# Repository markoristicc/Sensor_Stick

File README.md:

# Project Dragonfly Documentation

## Overview 

Project Dragonfly serves as a way to consolidate several low-profile sensors into a single, peripheral device, which attaches via USB to an drone in order to provide an estimation of state while keeping the device as small as possible. In doing so, we hope to create a modular, more cost effective way of providing state estimation, reducing the individual sensor configuration workload for drone manufacturers and hobbyists

The files containing the dragonfly PCB schematic and layout can be found in [PCB](https://github.com/markoristicc/Sensor_Stick/tree/prod/PCB), and the driver code can be found in the [SensorStick_integrated](https://github.com/markoristicc/Sensor_Stick/tree/prod/SensorStick_integrated) folder. This code was developed using the STM32CubeIDE, so that may be most convenient for you, however any embedded C development environment should suffice for flashing the code onto the PCB.  

## Getting Data off the Dragonfly for your own use

If you want to use the Dragonfly simply to collect data, we have provided code to do so, located in [UAVFirmware](https://github.com/markoristicc/Sensor_Stick/tree/prod/UAVFirmware) . If you are not already familiar with ROS, visiting [this](https://docs.ros.org/en/humble/Tutorials.html) documentation may be helpful, specifically the tutorials on creating a workspace, creating a package, writing a simply publisher & subscriber (python), and creating custom msg files. The code we are using assumes that you are running using ROS Humble on Ubuntu 22.02 and are using Python > 3 . 

In essence, this data parses the packet sent by the dragonfly and composes a custom message composed of the following message types: sensor_msgs/Imu, sensor_msgs/MagneticField, sensor_msgs/NavSatTransform, rosflight_msgs/Barometer, and rosflight_msgs/Airspeed. This message is published to the topic 'topic' (which can be changed in UAVFirmware/src/talker_listener/talker_listener/talker.py). To run the publisher enter the following commands into your terminal:

```
source /opt/ros/humble/setup.bash
colcon build --packages-select talker_listener 
```
On a separate terminal run
```
source install/setup.bash
ros2 run talker_listener talkerNode
```

And from there your ROS pubisher will be publishing data from the dragonfly to 'topic' at a rate of 100Hz!

## Performing Visualizations

If you want to perform visualizations using a state estimation computed from the measurements on the board, simply run the code located in [estimationVisualization](https://github.com/markoristicc/Sensor_Stick/tree/prod/estimationVisualization). This code assumes you are running ROS Melodic on Ubuntu 18.02, with Python 2.7 >. The library we use to perform estimation is [robot_localization](http://docs.ros.org/en/noetic/api/robot_localization/html/index.html) and the library for visualization is [RViz](http://wiki.ros.org/rviz). Although you should not need to read through the documentation to perform the visualizations, if you wish to modify any of the code for your own use reading them is **important**.

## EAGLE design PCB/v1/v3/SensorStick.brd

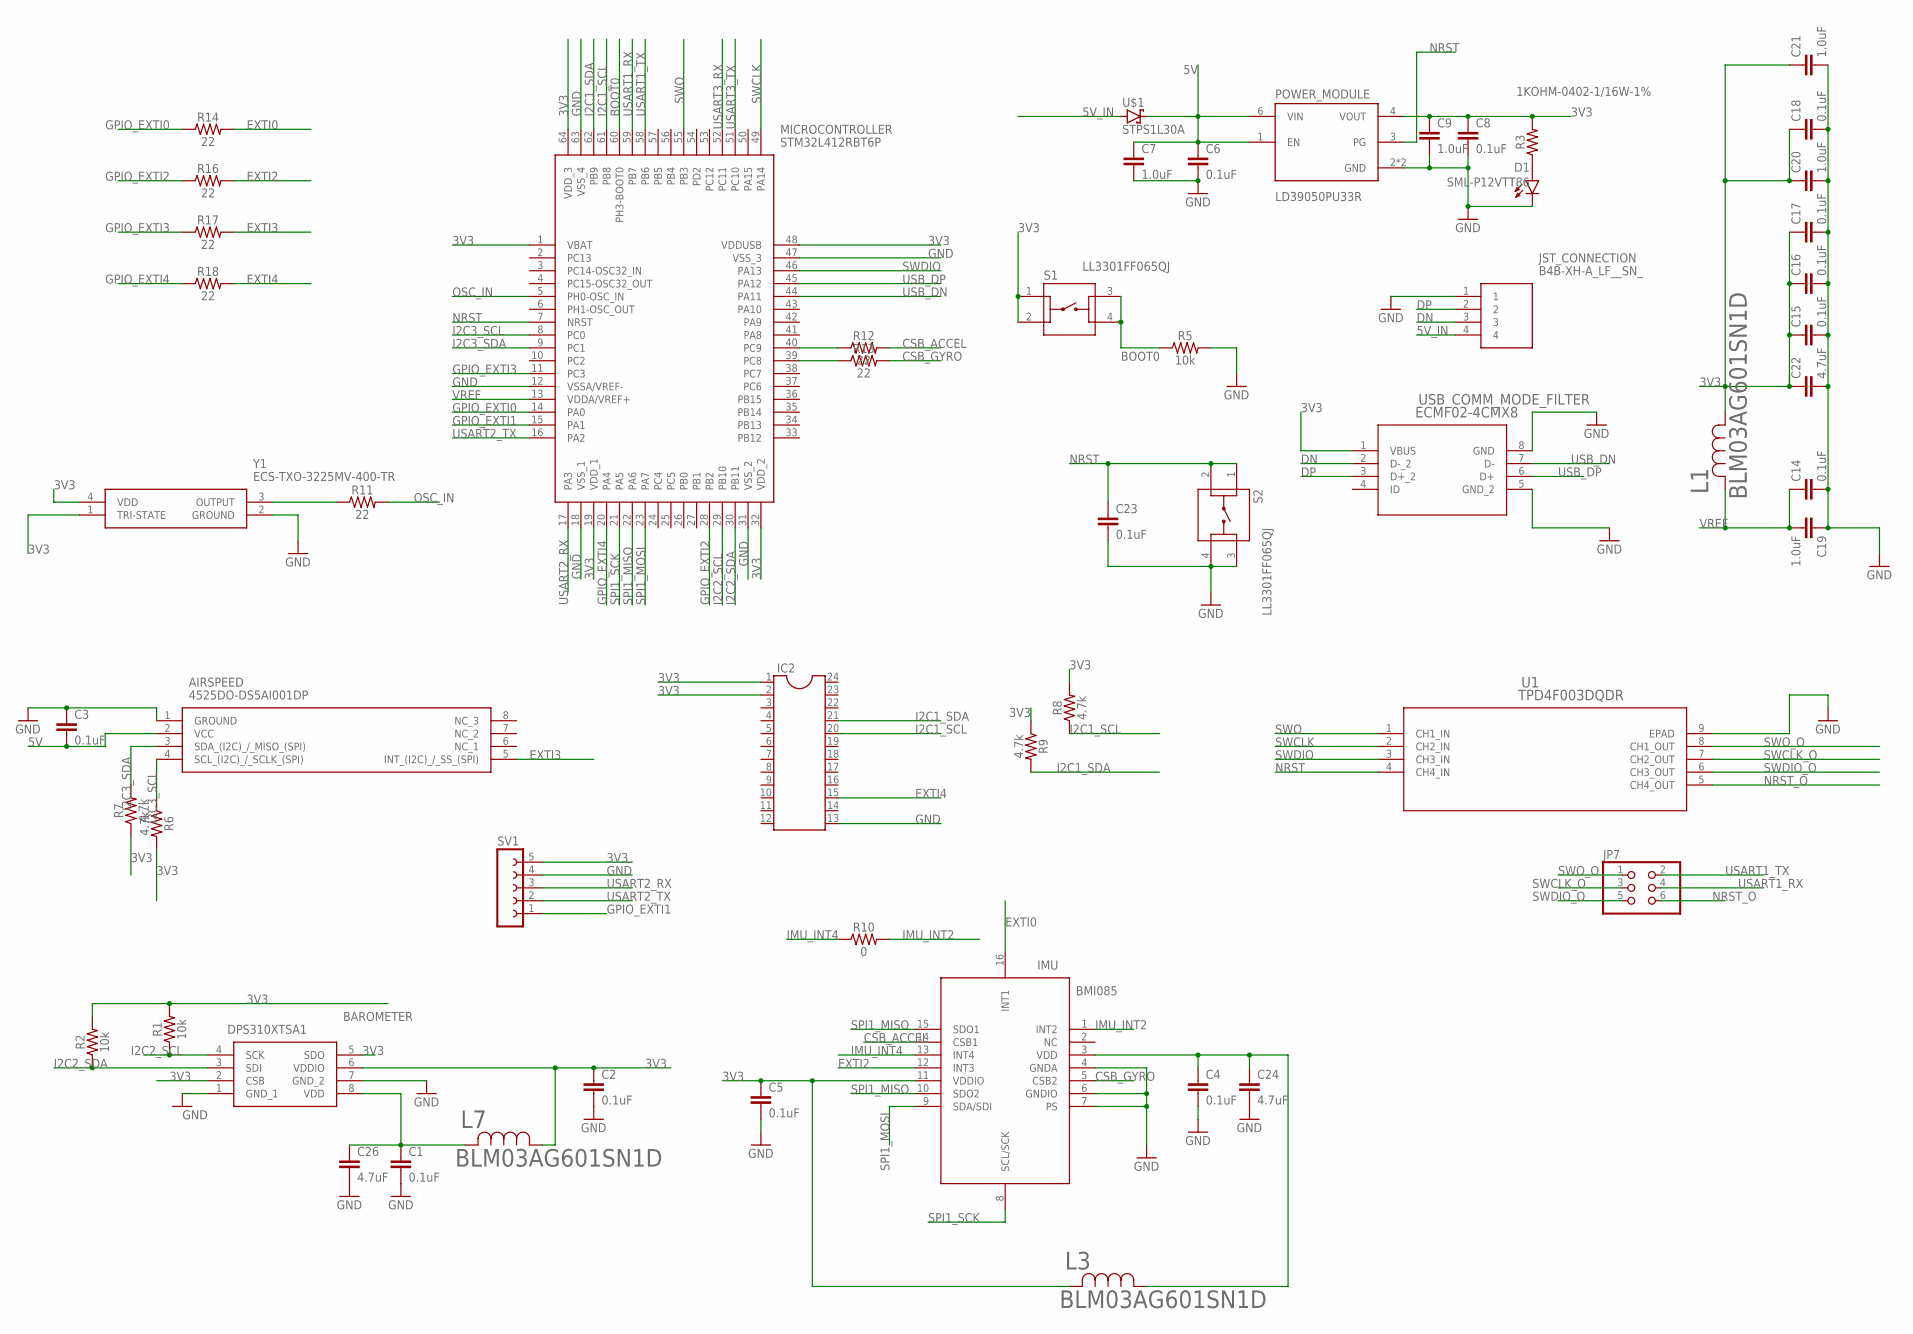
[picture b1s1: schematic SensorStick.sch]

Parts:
AIRSPEED: 4525DO-DS5AI001DP; 4525DO-DS...P
BAROMETER: DPS310XTSA1
C1, C2, C3, C4, C5, C6, C8: 0.1uF; 0402
C7, C9: 1.0uF; 0402
C14, C15, C16, C17, C18, C23: 0.1uF; 0603
C19, C20, C21: 1.0uF; 0805
C22, C24, C26: 4.7uF; 0603
D1: SML-P12VTT86; LED_SML-P11UTT86R
IC2: DIL24-6
IMU: BMI085
JP7: PINHD-2X3; 2X03
JST_CONNECTION: B4B-XH-A_LF__SN_; B4BXHALFSN
L1, L3, L7: BLM03AG601SN1D; IND_BLM03_0201_MUR
MICROCONTROLLER: STM32L412RBT6P; QFP50P1200X1200X160-64N
POWER_MODULE: LD39050PU33R; SON95P300X300X100-7N
R1, R2: 10k; 0402
R3: 1KOHM-0402-1/16W-1%; 0402
R5: 10k; 0603
R6, R7, R8, R9: 4.7k; 0603
R10: 0; 0603
R11, R12, R13, R14, R16, R17, R18: 22; 0402
S1, S2: LL3301FF065QJ
SV1: FE05-1
U1: TPD4F003DQDR; DQD8_1P2X0P4
U$1: STPS1L30A; DIOM5226X223N
USB_COMM_MODE_FILTER: ECMF02-4CMX8; MICRO_QFN-8L_STM
Y1: ECS-TXO-3225MV-400-TR; ECSTXO3225MV400TR

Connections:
3V3: BAROMETER.2 (CSB), BAROMETER.5 (SDO), BAROMETER.6 (VDDIO), C2.1, C5.1, C8.1, C9.1, C15.1, C16.1, C17.1, C18.1, C20.1, C21.1, C22.1, IC2.1, IC2.2, IMU.11 (VDDIO), L1.1, L3.2, L7.1, MICROCONTROLLER.1 (VBAT), MICROCONTROLLER.19 (VDD_1), MICROCONTROLLER.32 (VDD_2), MICROCONTROLLER.48 (VDDUSB), MICROCONTROLLER.64 (VDD_3), POWER_MODULE.4 (VOUT), R1.2, R2.2, R3.2, R6.2, R7.1, R8.2, R9.1, S1.1, S1.2, SV1.5, USB_COMM_MODE_FILTER.1 (VBUS), Y1.1 (TRI-STATE), Y1.4 (VDD)
5V: AIRSPEED.2 (VCC), C3.2, C6.1, C7.1, POWER_MODULE.1 (EN), POWER_MODULE.6 (VIN), U$1.1 (C)
5V_IN: JST_CONNECTION.4, U$1.2 (A)
BOOT0: MICROCONTROLLER.60 (PH3-BOOT0), R5.1, S1.3, S1.4
CSB_ACCEL: IMU.14 (CSB1), R12.2
CSB_GYRO: IMU.5 (CSB2), R13.2
DN: JST_CONNECTION.3, USB_COMM_MODE_FILTER.2 (D-_2)
DP: JST_CONNECTION.2, USB_COMM_MODE_FILTER.3 (D+_2)
EXTI0: IMU.16 (INT1), R14.2
EXTI2: IMU.12 (INT3), R16.2
EXTI3: AIRSPEED.5 (INT_(I2C)_/_SS_(SPI)), R17.2
EXTI4: IC2.15, R18.2
GND: AIRSPEED.1 (GROUND), BAROMETER.1 (GND_1), BAROMETER.7 (GND_2), C1.2, C2.2, C3.1, C4.2, C5.2, C6.2, C7.2, C8.2, C9.2, C14.2, C15.2, C16.2, C17.2, C18.2, C19.1, C20.2, C21.2, C22.2, C23.2, C24.2, C26.2, D1.C, IC2.13, IMU.4 (GNDA), IMU.6 (GNDIO), IMU.7 (PS), JST_CONNECTION.1, MICROCONTROLLER.12 (VSSA/VREF-), MICROCONTROLLER.18 (VSS_1), MICROCONTROLLER.31 (VSS_2), MICROCONTROLLER.47 (VSS_3), MICROCONTROLLER.63 (VSS_4), POWER_MODULE.2 (GND), POWER_MODULE.7 (GND), R5.2, S2.3, S2.4, SV1.4, U1.9 (EPAD), USB_COMM_MODE_FILTER.5 (GND_2), USB_COMM_MODE_FILTER.8 (GND), Y1.2 (GROUND)
GPIO_EXTI0: MICROCONTROLLER.14 (PA0), R14.1
GPIO_EXTI1: MICROCONTROLLER.15 (PA1), SV1.1
GPIO_EXTI2: MICROCONTROLLER.28 (PB2), R16.1
GPIO_EXTI3: MICROCONTROLLER.11 (PC3), R17.1
GPIO_EXTI4: MICROCONTROLLER.20 (PA4), R18.1
I2C1_SCL: IC2.20, MICROCONTROLLER.61 (PB8), R8.1
I2C1_SDA: IC2.21, MICROCONTROLLER.62 (PB9), R9.2
I2C2_SCL: BAROMETER.4 (SCK), MICROCONTROLLER.29 (PB10), R1.1
I2C2_SDA: BAROMETER.3 (SDI), MICROCONTROLLER.30 (PB11), R2.1
I2C3_SCL: AIRSPEED.4 (SCL_(I2C)_/_SCLK_(SPI)), MICROCONTROLLER.8 (PC0), R6.1
I2C3_SDA: AIRSPEED.3 (SDA_(I2C)_/_MISO_(SPI)), MICROCONTROLLER.9 (PC1), R7.2
IMU_INT2: IMU.1 (INT2), R10.2
IMU_INT4: IMU.13 (INT4), R10.1
unnamed: R11.1, Y1.3 (OUTPUT)
unnamed: MICROCONTROLLER.40 (PC9), R12.1
unnamed: MICROCONTROLLER.39 (PC8), R13.1
unnamed: D1.A, R3.1
unnamed: BAROMETER.8 (VDD), C1.1, C26.1, L7.2
unnamed: C4.1, C24.1, IMU.3 (VDD), L3.1
NRST: C23.1, MICROCONTROLLER.7 (NRST), POWER_MODULE.3 (PG), S2.1, S2.2, U1.4 (CH4_IN)
NRST_O: JP7.6, U1.5 (CH4_OUT)
OSC_IN: MICROCONTROLLER.5 (PH0-OSC_IN), R11.2
SPI1_MISO: IMU.10 (SDO2), IMU.15 (SDO1), MICROCONTROLLER.22 (PA6)
SPI1_MOSI: IMU.9 (SDA/SDI), MICROCONTROLLER.23 (PA7)
SPI1_SCK: IMU.8 (SCL/SCK), MICROCONTROLLER.21 (PA5)
SWCLK: MICROCONTROLLER.49 (PA14), U1.2 (CH2_IN)
SWCLK_O: JP7.3, U1.7 (CH2_OUT)
SWDIO: MICROCONTROLLER.46 (PA13), U1.3 (CH3_IN)
SWDIO_O: JP7.5, U1.6 (CH3_OUT)
SWO: MICROCONTROLLER.55 (PB3), U1.1 (CH1_IN)
SWO_O: JP7.1, U1.8 (CH1_OUT)
USART1_RX: JP7.4, MICROCONTROLLER.59 (PB7)
USART1_TX: JP7.2, MICROCONTROLLER.58 (PB6)
USART2_RX: MICROCONTROLLER.17 (PA3), SV1.3
USART2_TX: MICROCONTROLLER.16 (PA2), SV1.2
USART3_RX: MICROCONTROLLER.52 (PC11)
USART3_TX: MICROCONTROLLER.51 (PC10)
USB_DN: MICROCONTROLLER.44 (PA11), USB_COMM_MODE_FILTER.7 (D-)
USB_DP: MICROCONTROLLER.45 (PA12), USB_COMM_MODE_FILTER.6 (D+)
VREF: C14.1, C19.2, L1.2, MICROCONTROLLER.13 (VDDA/VREF+)

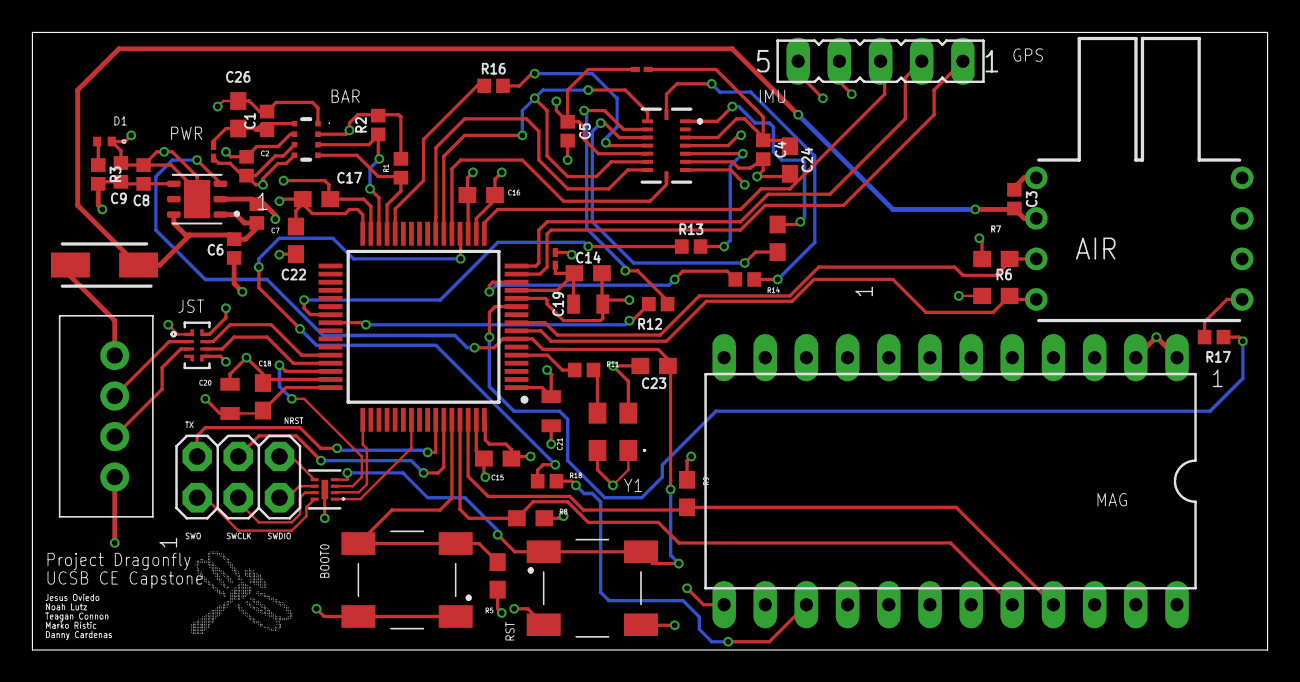
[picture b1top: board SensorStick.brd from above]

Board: 4 copper layers, 76.2 x 38.1 mm, 56 parts (0 on the bottom side), 51 nets.

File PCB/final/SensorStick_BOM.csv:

Comment,Designator,Footprint,LCSC Part #
,JP7,2X03,C65114
,IC2,DIL24-6,
,SV1,FE05-1,
0,R10,603, C21189
0.1uF,C1 C2 C3 C4 C5 C6 C8,402,C1525
0.1uF,C14 C15 C16 C17 C18 C23,603,C14663
1.0uF,C7 C9,402,C52923
1.0uF,C19 C20 C21,805,C28323
1KOHM-0402-1/16W-1%,R3,402, C22790
4.7k,R6 R7 R8 R9,603,C23162
4.7uF,C22 C24 C26,603,C19666
10k,R1 R2,402,C25744
10k,R5,603,C25804
22,R11 R12 R13 R14 R16 R17 R18,402,C25092
4525DO-DS5AI001DP,AIRSPEED,4525DO-DS...P,
B4B-XH-A_LF__SN_,JST_CONNECTION,B4BXHALFSN,C144395
BLM03AG601SN1D,L1 L3 L7,IND_BLM03_0201_MUR, C85811
BMI085,IMU,BMI085, C194919
DPS310XTSA1,BAROMETER,DPS310XTSA1,C130156
ECMF02-4CMX8,USB_COMM_MODE_FILTER,MICRO_QFN-8L_STM,C717678
ECS-TXO-3225MV-400-TR,Y1,ECSTXO3225MV400TR,C253725
LD39050PU33R,POWER_MODULE,SON95P300X300X100-7N,C132827
LL3301FF065QJ,S1 S2,LL3301FF065QJ,C273521
SML-P12VTT86,D1,LED_SML-P11UTT86R,C136765
STM32L412RBT6P,MICROCONTROLLER,QFP50P1200X1200X160-64N,C1339033
STPS1L30A,U$1,DIOM5226X223N,C157388
TPD4F003DQDR,U1,DQD8_1P2X0P4,C398926

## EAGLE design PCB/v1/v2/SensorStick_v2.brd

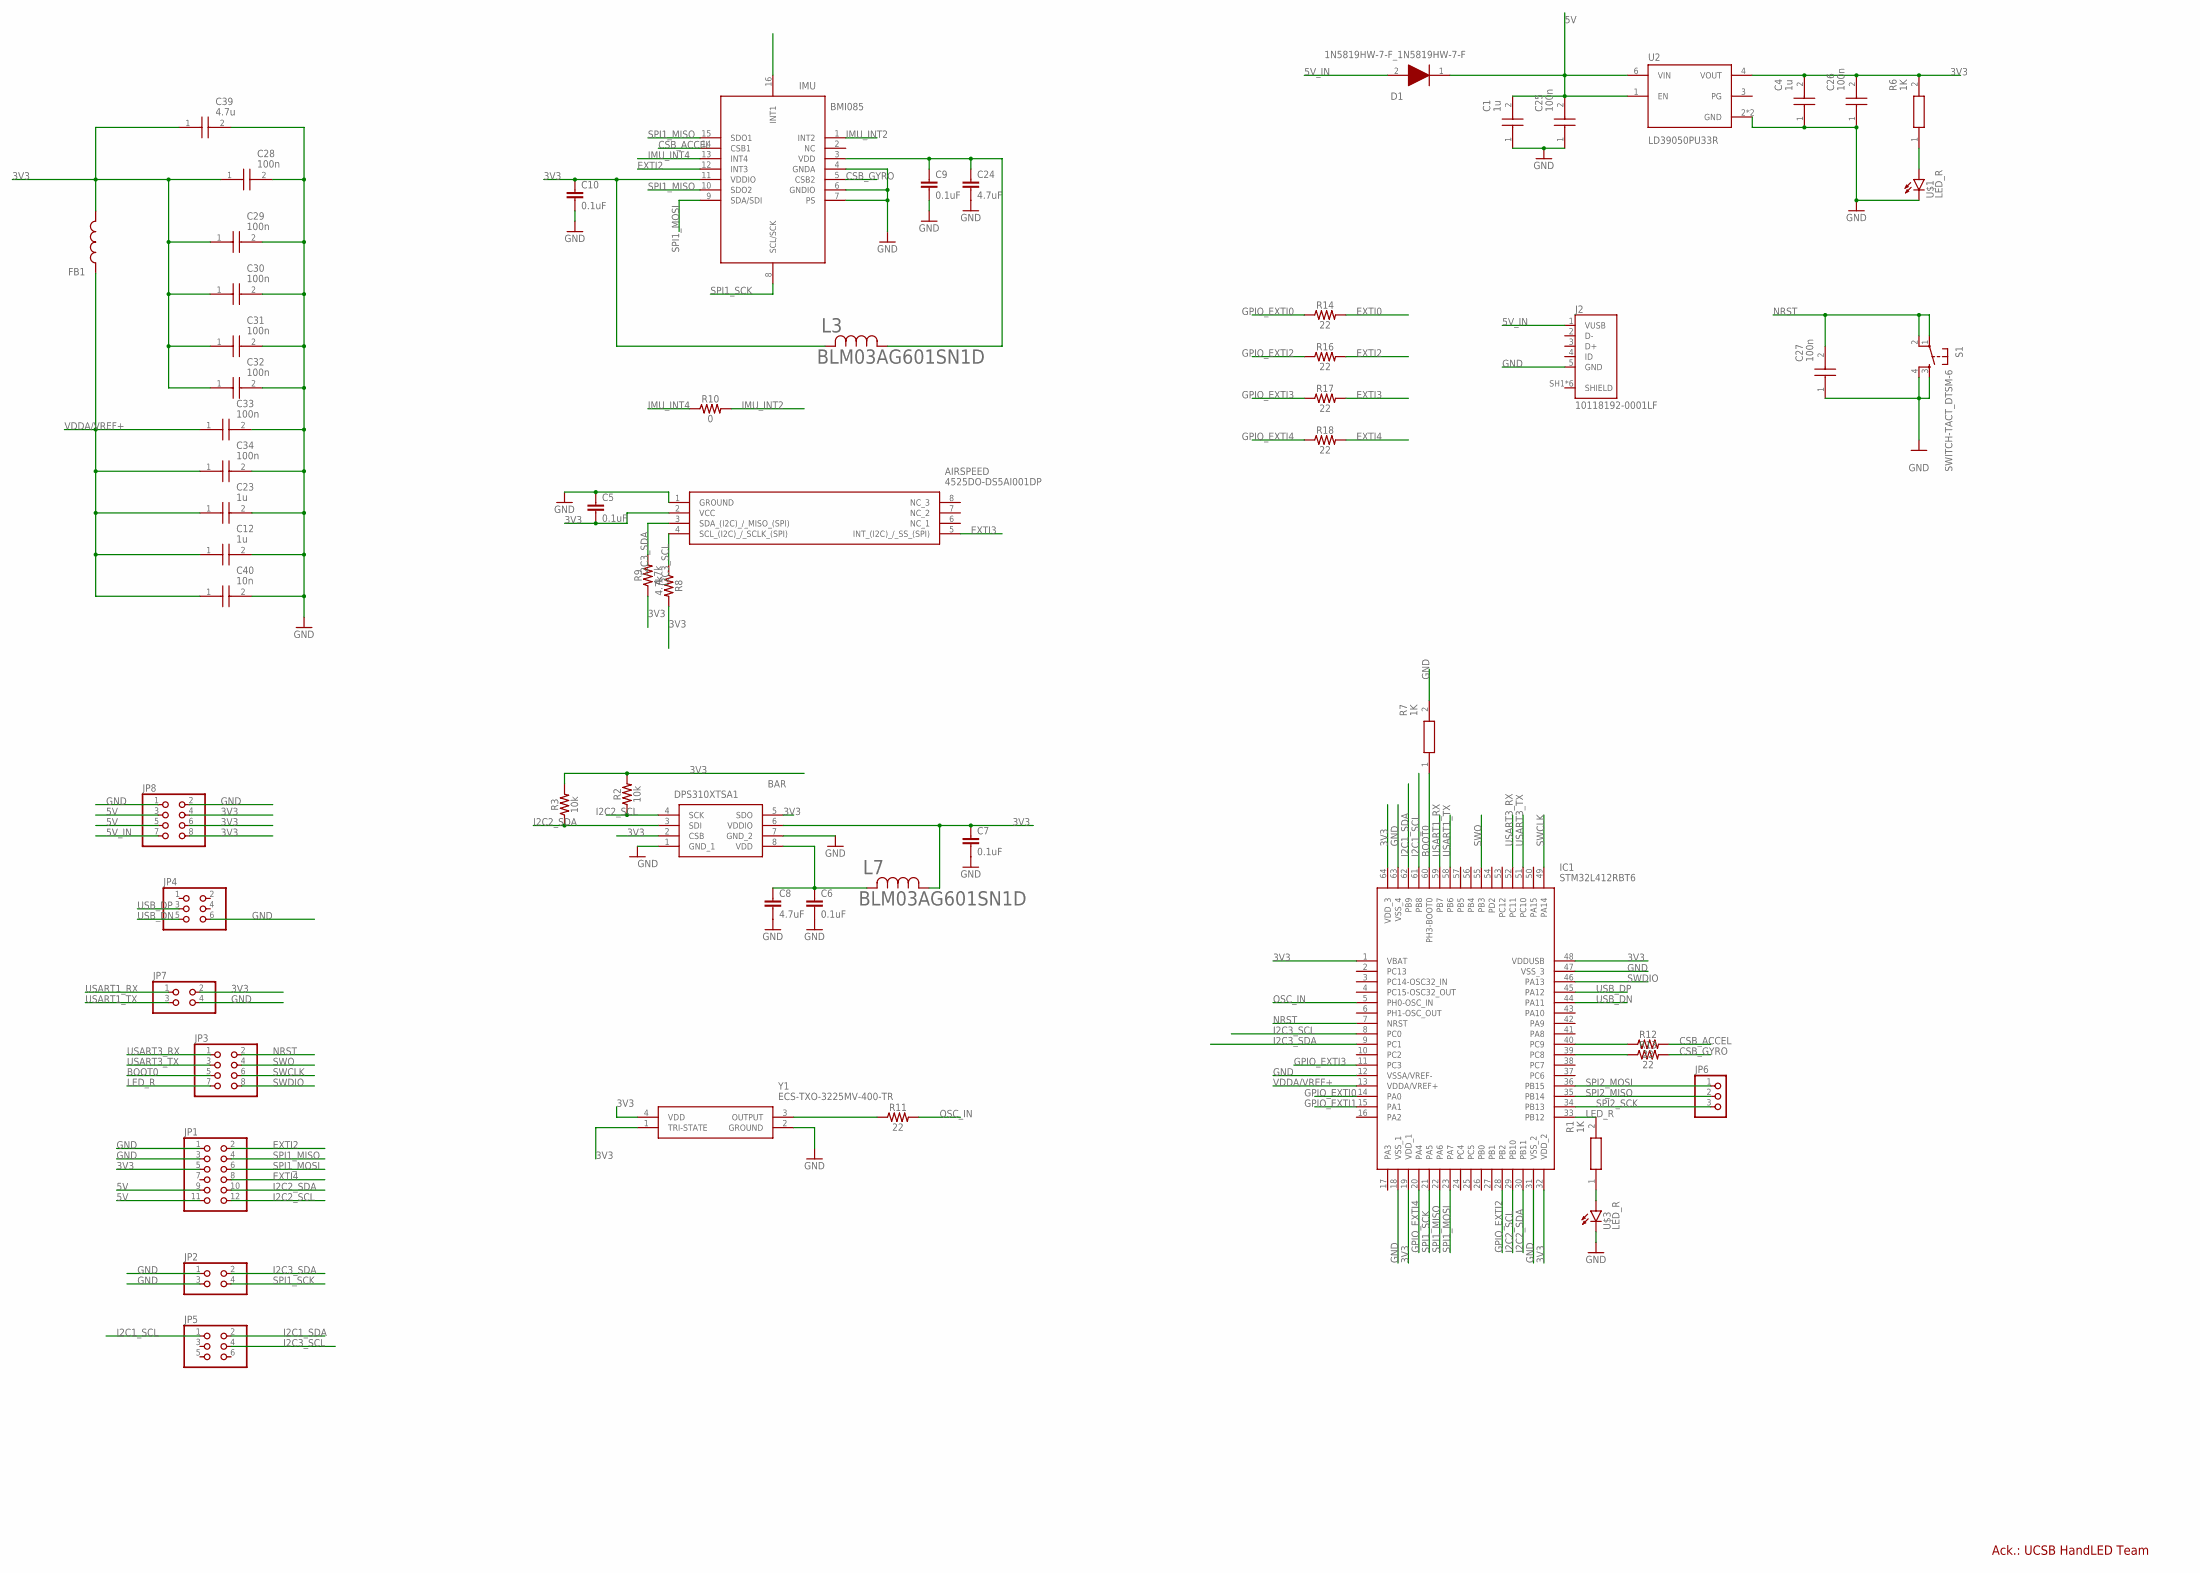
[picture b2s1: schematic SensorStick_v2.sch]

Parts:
AIRSPEED: 4525DO-DS5AI001DP; 4525DO-DS...P
BAR: DPS310XTSA1
C1, C4, C12, C23: 1u; CAPC2012X95N
C5, C6, C7, C9, C10: 0.1uF; 0402
C8, C24: 4.7uF; 0603
C25, C26, C27, C28, C29, C30, C31, C32, C33, C34: 100n; CAPC3216X180N
C39: 4.7u; CAPC2012X145N
C40: 10n; CAPC3216X180N
D1: 1N5819HW-7-F_1N5819HW-7-F; 1N5819HW-7-F_SOD3716X145N
FB1: BK1608HS601-T; BEADC1608X95N
IC1: STM32L412RBT6; QFP50P1200X1200X160-64N
IMU: BMI085
J2: 10118192-0001LF; AMPHENOL_10118192-0001LF
JP1: PINHD-2X6; 2X06
JP2, JP7: PINHD-2X2; 2X02
JP3, JP8: PINHD-2X4; 2X04
JP4, JP5: PINHD-2X3; 2X03
JP6: PINHD-1X3; 1X03
L3, L7: BLM03AG601SN1D; IND_BLM03_0201_MUR
R1, R6, R7: 1K; RESC2012X60N
R2, R3: 10k; 0402
R8, R9: 4.7k; 0603
R10: 0; 0603
R11, R12, R13, R14, R16, R17, R18: 22; 0402
S1: SWITCH-TACT_DTSM-6
U2: LD39050PU33R; SON95P300X300X100-7N
U$1, U$3: LED_R; LED_SML-P11UTT86R
Y1: ECS-TXO-3225MV-400-TR; ECSTXO3225MV400TR

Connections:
3V3: AIRSPEED.2 (VCC), BAR.2 (CSB), BAR.5 (SDO), BAR.6 (VDDIO), C4.2, C5.2, C7.1, C10.1, C26.2, C28.1, C29.1, C30.1, C31.1, C32.1, C39.1, FB1.2, IC1.1 (VBAT), IC1.19 (VDD_1), IC1.32 (VDD_2), IC1.48 (VDDUSB), IC1.64 (VDD_3), IMU.11 (VDDIO), JP1.5, JP7.2, JP8.4, JP8.6, JP8.8, L3.2, L7.1, R2.2, R3.2, R6.2, R8.2, R9.1, U2.4 (VOUT), Y1.1 (TRI-STATE), Y1.4 (VDD)
5V: C1.2, C25.2, D1.1 (K), JP1.9, JP1.11, JP8.3, JP8.5, U2.1 (EN), U2.6 (VIN)
5V_IN: D1.2 (A), J2.1 (VUSB), JP8.7
BOOT0: IC1.60 (PH3-BOOT0), JP3.5, R7.1
CSB_ACCEL: IMU.14 (CSB1), R12.2
CSB_GYRO: IMU.5 (CSB2), R13.2
EXTI0: IMU.16 (INT1), R14.2
EXTI2: IMU.12 (INT3), JP1.2, R16.2
EXTI3: AIRSPEED.5 (INT_(I2C)_/_SS_(SPI)), R17.2
EXTI4: JP1.8, R18.2
GND: AIRSPEED.1 (GROUND), BAR.1 (GND_1), BAR.7 (GND_2), C1.1, C4.1, C5.1, C6.2, C7.2, C8.2, C9.2, C10.2, C12.2, C23.2, C24.2, C25.1, C26.1, C27.1, C28.2, C29.2, C30.2, C31.2, C32.2, C33.2, C34.2, C39.2, C40.2, IC1.12 (VSSA/VREF-), IC1.18 (VSS_1), IC1.31 (VSS_2), IC1.47 (VSS_3), IC1.63 (VSS_4), IMU.4 (GNDA), IMU.6 (GNDIO), IMU.7 (PS), J2.5 (GND), JP1.1, JP1.3, JP2.1, JP2.3, JP4.6, JP7.4, JP8.1, JP8.2, R7.2, S1.3, S1.4, U2.2 (GND), U2.7 (GND), U$1.C, U$3.C, Y1.2 (GROUND)
GPIO_EXTI0: IC1.14 (PA0), R14.1
GPIO_EXTI1: IC1.15 (PA1)
GPIO_EXTI2: IC1.28 (PB2), R16.1
GPIO_EXTI3: IC1.11 (PC3), R17.1
GPIO_EXTI4: IC1.20 (PA4), R18.1
I2C1_SCL: IC1.61 (PB8), JP5.1
I2C1_SDA: IC1.62 (PB9), JP5.2
I2C2_SCL: BAR.4 (SCK), IC1.29 (PB10), JP1.12, R2.1
I2C2_SDA: BAR.3 (SDI), IC1.30 (PB11), JP1.10, R3.1
I2C3_SCL: AIRSPEED.4 (SCL_(I2C)_/_SCLK_(SPI)), IC1.8 (PC0), JP5.4, R8.1
I2C3_SDA: AIRSPEED.3 (SDA_(I2C)_/_MISO_(SPI)), IC1.9 (PC1), JP2.2, R9.2
IMU_INT2: IMU.1 (INT2), R10.2
IMU_INT4: IMU.13 (INT4), R10.1
LED_R: IC1.33 (PB12), JP3.7, R1.2
unnamed: IC1.39 (PC8), R13.1
unnamed: R1.1, U$3.A
unnamed: R11.1, Y1.3 (OUTPUT)
unnamed: IC1.40 (PC9), R12.1
unnamed: R6.1, U$1.A
unnamed: BAR.8 (VDD), C6.1, C8.1, L7.2
unnamed: C9.1, C24.1, IMU.3 (VDD), L3.1
NRST: C27.2, IC1.7 (NRST), JP3.2, S1.1, S1.2
OSC_IN: IC1.5 (PH0-OSC_IN), R11.2
SPI1_MISO: IC1.22 (PA6), IMU.10 (SDO2), IMU.15 (SDO1), JP1.4
SPI1_MOSI: IC1.23 (PA7), IMU.9 (SDA/SDI), JP1.6
SPI1_SCK: IC1.21 (PA5), IMU.8 (SCL/SCK), JP2.4
SPI2_MISO: IC1.35 (PB14), JP6.2
SPI2_MOSI: IC1.36 (PB15), JP6.1
SPI2_SCK: IC1.34 (PB13), JP6.3
SWCLK: IC1.49 (PA14), JP3.6
SWDIO: IC1.46 (PA13), JP3.8
SWO: IC1.55 (PB3), JP3.4
USART1_RX: IC1.59 (PB7), JP7.1
USART1_TX: IC1.58 (PB6), JP7.3
USART3_RX: IC1.52 (PC11), JP3.1
USART3_TX: IC1.51 (PC10), JP3.3
USB_DN: IC1.44 (PA11), JP4.5
USB_DP: IC1.45 (PA12), JP4.3
VDDA/VREF+: C12.1, C23.1, C33.1, C34.1, C40.1, FB1.1, IC1.13 (VDDA/VREF+)

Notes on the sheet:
Ack.: UCSB HandLED Team

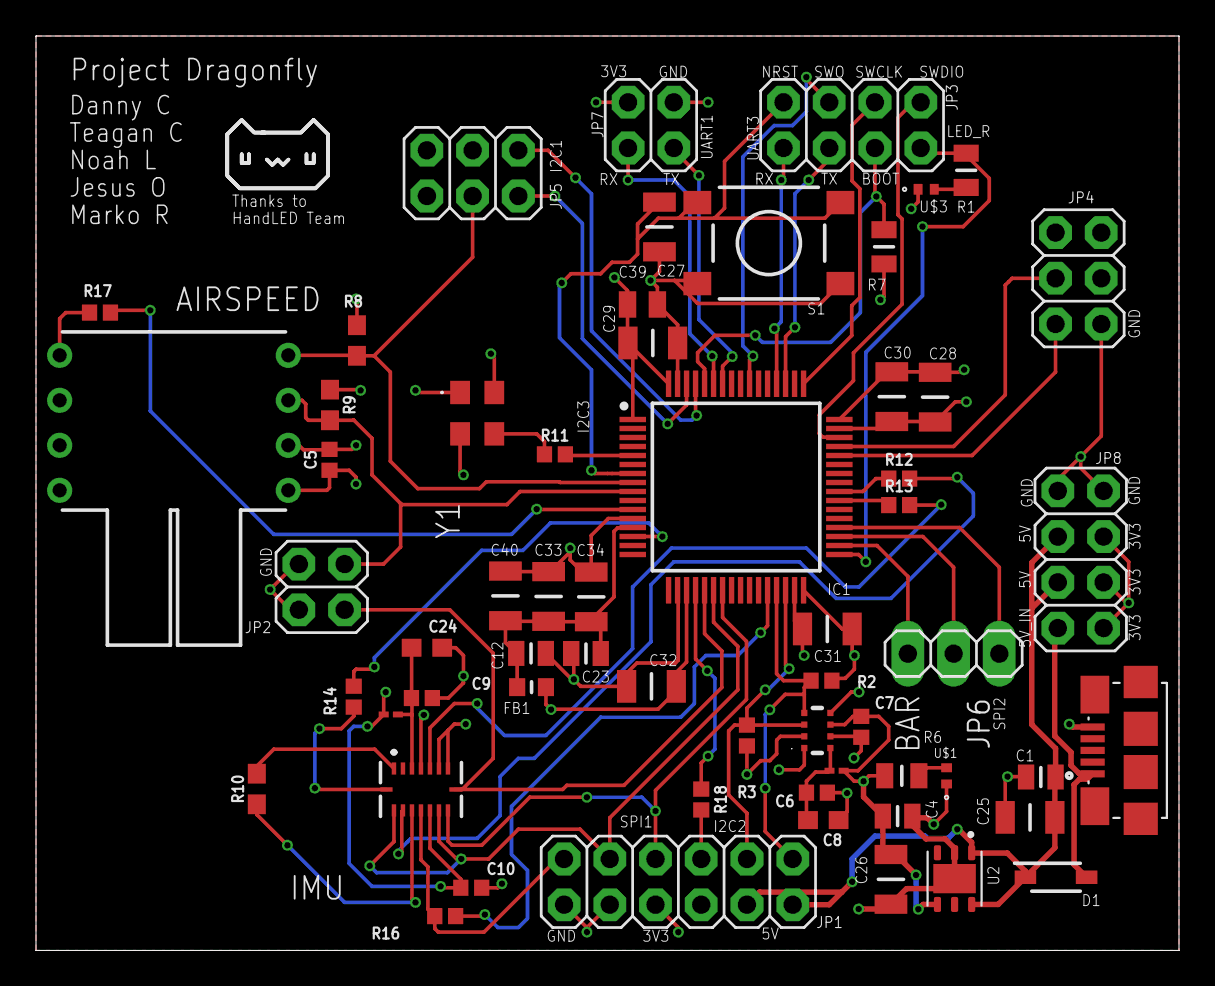
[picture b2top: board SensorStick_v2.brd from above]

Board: 4 copper layers, 63.5 x 50.8 mm, 60 parts (0 on the bottom side), 49 nets.

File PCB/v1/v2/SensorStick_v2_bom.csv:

Comment,Designator,Footprint,LCSC Part #
,JP6,1X03,C180248
,JP2,2X02,C124420
,JP7,2X02,C124420
,JP4,2X03,C718233
,JP5,2X03,C718233
,JP3,2X04,C358726
,JP8,2X04,C358726
,JP1,2X06,C718230
0,R10,603,C21189
0.1uF,C5 C6 C7 C9 C10,402,C107000
1K,R1 R6 R7,RESC2012X60N,C100047
1N5819HW-7-F_1N5819HW-7-F,D1,1N5819HW-7-F_SOD3716X145N,C82544
1u,C1 C4 C12 C23,CAPC2012X95N,C94122
4.7k,R8 R9,603,C23162
4.7u,C39,CAPC2012X145N,C520074
4.7uF,C8 C24,603,C19666
10k,R2 R3,402,C25744
10n,C40,CAPC3216X180N,C107201
22,R11 R12 R13 R14 R16 R17 R18,402,C25092
100n,C25 C26 C27 C28 C29 C30 C31 C32 C33 C34,CAPC3216X180N,C107181
4525DO-DS5AI001DP,AIRSPEED,4525DO-DS...P,
10118192-0001LF,J2,AMPHENOL_10118192-0001LF,C132564
BK1608HS601-T,FB1,BEADC1608X95N,C222675
BLM03AG601SN1D,L3 L7,IND_BLM03_0201_MUR,C85811
BMI085,IMU,BMI085,C194919
DPS310XTSA1,BAR,DPS310XTSA1,C130156
ECS-TXO-3225MV-400-TR,Y1,ECSTXO3225MV400TR,C253725
LD39050PU33R,U2,SON95P300X300X100-7N,C132827
LED_R,U$1 U$3,LED_SML-P11UTT86R,C71911
STM32L412RBT6,IC1,QFP50P1200X1200X160-64N,C1339033
SWITCH-TACT_DTSM-6,S1,SWITCH-TACT_DTSM-6,C483769

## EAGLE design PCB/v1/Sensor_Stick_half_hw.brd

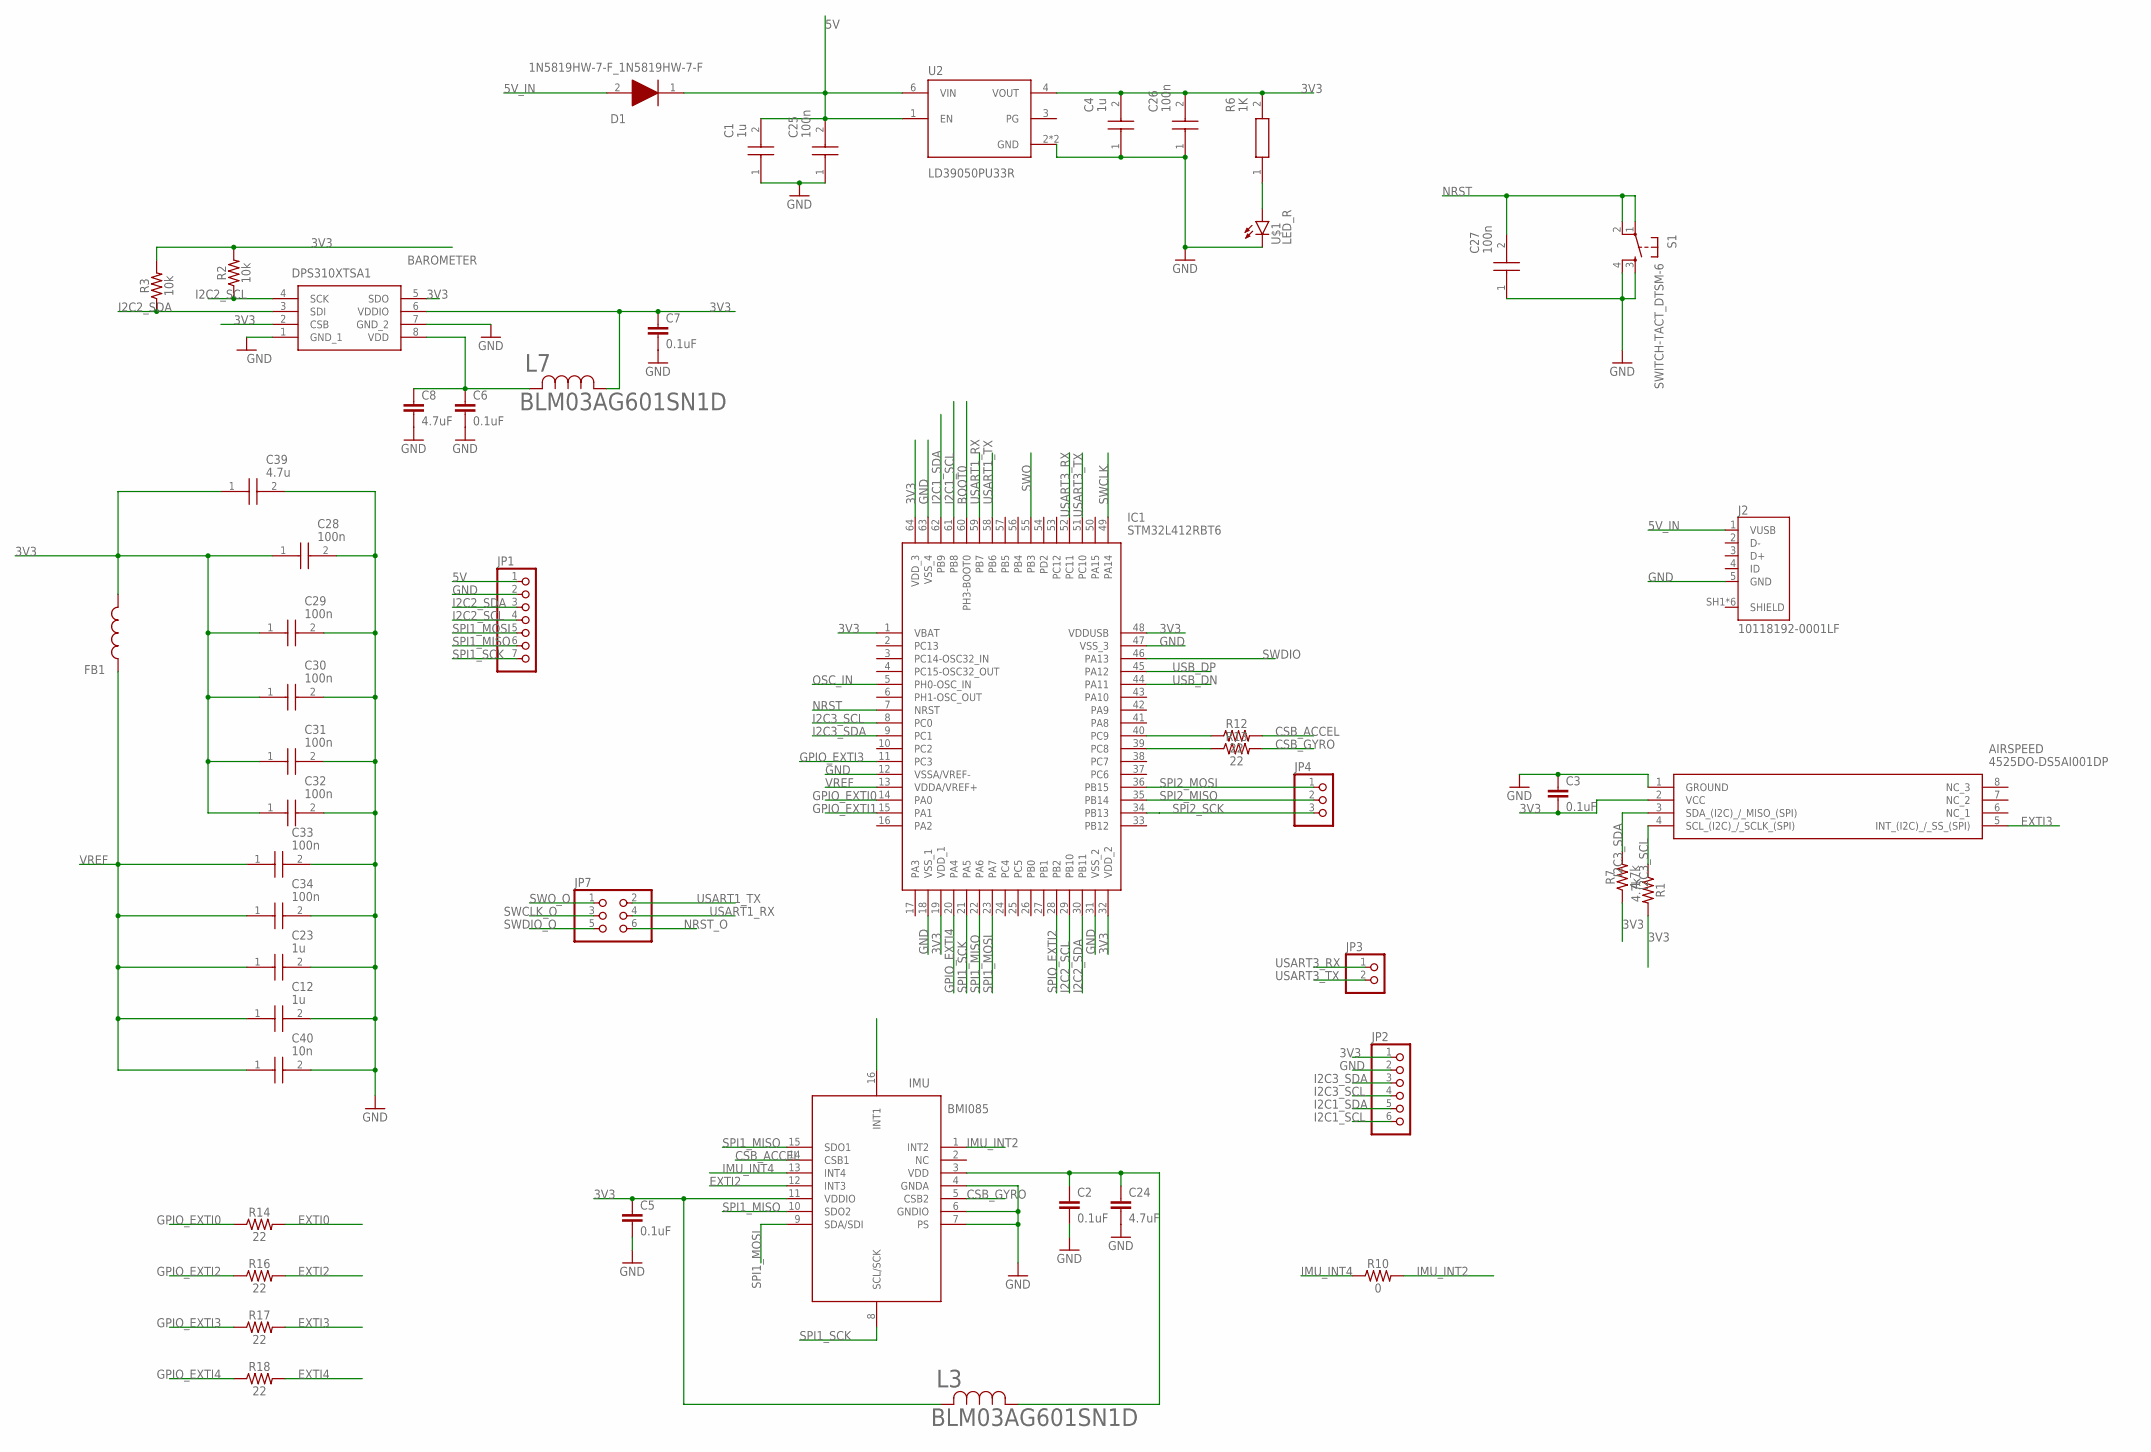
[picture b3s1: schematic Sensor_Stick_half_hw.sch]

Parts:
AIRSPEED: 4525DO-DS5AI001DP; 4525DO-DS...P
BAROMETER: DPS310XTSA1
C1, C4, C12, C23: 1u; CAPC2012X95N
C2, C3, C5, C6, C7: 0.1uF; 0402
C8, C24: 4.7uF; 0603
C25, C26, C27, C28, C29, C30, C31, C32, C33, C34: 100n; CAPC3216X180N
C39: 4.7u; CAPC2012X145N
C40: 10n; CAPC3216X180N
D1: 1N5819HW-7-F_1N5819HW-7-F; 1N5819HW-7-F_SOD3716X145N
FB1: BK1608HS601-T; BEADC1608X95N
IC1: STM32L412RBT6; QFP50P1200X1200X160-64N
IMU: BMI085
J2: 10118192-0001LF; AMPHENOL_10118192-0001LF
JP1: PINHD-1X7; 1X07
JP2: PINHD-1X6; 1X06
JP3: PINHD-1X2; 1X02
JP4: PINHD-1X3; 1X03
JP7: PINHD-2X3; 2X03
L3, L7: BLM03AG601SN1D; IND_BLM03_0201_MUR
R1, R7: 4.7k; 0603
R2, R3: 10k; 0402
R6: 1K; RESC2012X60N
R10: 0; 0603
R12, R13, R14, R16, R17, R18: 22; 0402
S1: SWITCH-TACT_DTSM-6
U2: LD39050PU33R; SON95P300X300X100-7N
U$1: LED_R; LED_SML-P11UTT86R

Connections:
3V3: AIRSPEED.2 (VCC), BAROMETER.2 (CSB), BAROMETER.5 (SDO), BAROMETER.6 (VDDIO), C3.2, C4.2, C5.1, C7.1, C26.2, C28.1, C29.1, C30.1, C31.1, C32.1, C39.1, FB1.2, IC1.1 (VBAT), IC1.19 (VDD_1), IC1.32 (VDD_2), IC1.48 (VDDUSB), IC1.64 (VDD_3), IMU.11 (VDDIO), JP2.1, L3.2, L7.1, R1.2, R2.2, R3.2, R6.2, R7.1, U2.4 (VOUT)
5V: C1.2, C25.2, D1.1 (K), JP1.1, U2.1 (EN), U2.6 (VIN)
5V_IN: D1.2 (A), J2.1 (VUSB)
BOOT0: IC1.60 (PH3-BOOT0)
CSB_ACCEL: IMU.14 (CSB1), R12.2
CSB_GYRO: IMU.5 (CSB2), R13.2
EXTI0: IMU.16 (INT1), R14.2
EXTI2: IMU.12 (INT3), R16.2
EXTI3: AIRSPEED.5 (INT_(I2C)_/_SS_(SPI)), R17.2
EXTI4: R18.2
GND: AIRSPEED.1 (GROUND), BAROMETER.1 (GND_1), BAROMETER.7 (GND_2), C1.1, C2.2, C3.1, C4.1, C5.2, C6.2, C7.2, C8.2, C12.2, C23.2, C24.2, C25.1, C26.1, C27.1, C28.2, C29.2, C30.2, C31.2, C32.2, C33.2, C34.2, C39.2, C40.2, IC1.12 (VSSA/VREF-), IC1.18 (VSS_1), IC1.31 (VSS_2), IC1.47 (VSS_3), IC1.63 (VSS_4), IMU.4 (GNDA), IMU.6 (GNDIO), IMU.7 (PS), J2.5 (GND), JP1.2, JP2.2, S1.3, S1.4, U2.2 (GND), U2.7 (GND), U$1.C
GPIO_EXTI0: IC1.14 (PA0), R14.1
GPIO_EXTI1: IC1.15 (PA1)
GPIO_EXTI2: R16.1
GPIO_EXTI3: IC1.11 (PC3), R17.1
GPIO_EXTI4: IC1.20 (PA4), R18.1
I2C1_SCL: IC1.61 (PB8), JP2.6
I2C1_SDA: IC1.62 (PB9), JP2.5
I2C2_SCL: BAROMETER.4 (SCK), IC1.29 (PB10), JP1.4, R2.1
I2C2_SDA: BAROMETER.3 (SDI), IC1.30 (PB11), JP1.3, R3.1
I2C3_SCL: AIRSPEED.4 (SCL_(I2C)_/_SCLK_(SPI)), IC1.8 (PC0), JP2.4, R1.1
I2C3_SDA: AIRSPEED.3 (SDA_(I2C)_/_MISO_(SPI)), IC1.9 (PC1), JP2.3, R7.2
IMU_INT2: IMU.1 (INT2), R10.2
IMU_INT4: IMU.13 (INT4), R10.1
unnamed: IC1.39 (PC8), R13.1
unnamed: IC1.40 (PC9), R12.1
unnamed: R6.1, U$1.A
unnamed: BAROMETER.8 (VDD), C6.1, C8.1, L7.2
unnamed: C2.1, C24.1, IMU.3 (VDD), L3.1
NRST: C27.2, IC1.7 (NRST), S1.1, S1.2
NRST_O: JP7.6
OSC_IN: IC1.5 (PH0-OSC_IN)
SPI1_MISO: IC1.22 (PA6), IMU.10 (SDO2), IMU.15 (SDO1), JP1.6
SPI1_MOSI: IC1.23 (PA7), IMU.9 (SDA/SDI), JP1.5
SPI1_SCK: IC1.21 (PA5), IMU.8 (SCL/SCK), JP1.7
SPI2_MISO: IC1.35 (PB14), JP4.2
SPI2_MOSI: IC1.36 (PB15), JP4.1
SPI2_SCK: IC1.34 (PB13), JP4.3
SPIO_EXTI2: IC1.28 (PB2)
SWCLK: IC1.49 (PA14)
SWCLK_O: JP7.3
SWDIO: IC1.46 (PA13)
SWDIO_O: JP7.5
SWO: IC1.55 (PB3)
SWO_O: JP7.1
USART1_RX: IC1.59 (PB7), JP7.4
USART1_TX: IC1.58 (PB6), JP7.2
USART3_RX: IC1.52 (PC11), JP3.1
USART3_TX: IC1.51 (PC10), JP3.2
USB_DN: IC1.44 (PA11)
USB_DP: IC1.45 (PA12)
VREF: C12.1, C23.1, C33.1, C34.1, C40.1, FB1.1, IC1.13 (VDDA/VREF+)

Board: 2 copper layers, 52 parts (0 on the bottom side), 37 nets, no tracks yet.

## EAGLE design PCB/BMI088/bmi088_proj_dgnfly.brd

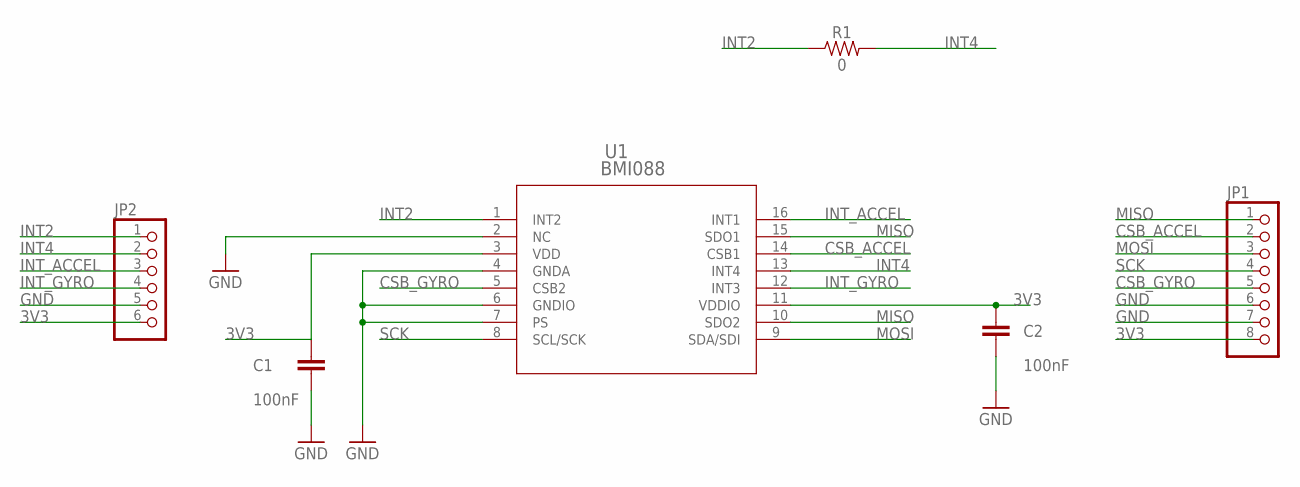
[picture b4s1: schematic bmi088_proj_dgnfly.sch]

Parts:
C1, C2: 100nF; CAPC1005X55N
JP1: PINHD-1X8; 1X08
JP2: PINHD-1X6; 1X06
R1: 0; 0603
U1: BMI088; QFN_BMI085_BOS

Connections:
3V3: C1.1, C2.1, JP1.8, JP2.6, U1.3 (VDD), U1.11 (VDDIO)
CSB_ACCEL: JP1.2, U1.14 (CSB1)
CSB_GYRO: JP1.5, U1.5 (CSB2)
GND: C1.2, C2.2, JP1.6, JP1.7, JP2.5, U1.2 (NC), U1.4 (GNDA), U1.6 (GNDIO), U1.7 (PS)
INT2: JP2.1, R1.1, U1.1 (INT2)
INT4: JP2.2, R1.2, U1.13 (INT4)
INT_ACCEL: JP2.3, U1.16 (INT1)
INT_GYRO: JP2.4, U1.12 (INT3)
MISO: JP1.1, U1.10 (SDO2), U1.15 (SDO1)
MOSI: JP1.3, U1.9 (SDA/SDI)
SCK: JP1.4, U1.8 (SCL/SCK)

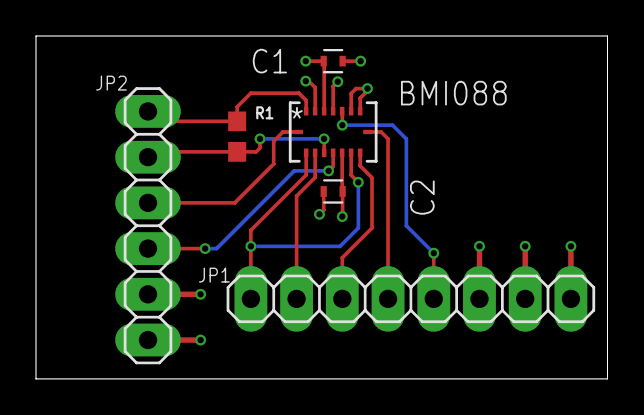
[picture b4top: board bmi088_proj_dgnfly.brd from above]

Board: 4 copper layers, 31.8 x 19.1 mm, 6 parts (0 on the bottom side), 11 nets.

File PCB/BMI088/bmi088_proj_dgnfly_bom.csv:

Comment,Designator,Footprint,LCSC Part #
,JP2,1X06,C37208
,JP1,1X08,C2894931
0,R1,603,C21189
100nF,C1 C2,CAPC1005X55N,C385888
BMI088,U1,QFN_BMI085_BOS,C194919

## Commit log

2022-12-01 Jesus - Adding folder for IMU driver + current code
2022-12-02 added airspeed sensor code
2022-12-02 Create temp
2023-01-11 updated sch
2023-01-20 Jesus - Updated IMU schematic
2023-01-21 added header pins to update IMU sch
2023-01-24 Jesus - MOst recent progress on layout
2023-01-25 updating dp sensor code
2023-01-25 Create DPSensor
2023-01-25 updated DP sensor code
2023-01-27 J - Current PCB layout, USB-C and power needed
2023-01-27 J- Added power supply module to layout, missing USB-C
2023-01-27 J- Edited data ready lines and connections, Barometer missing
2023-01-27 J- Connected interrupt line for barometer
2023-01-27 J - Added header pins for remaining I2C lines
2023-01-27 Added in JST connection and renamed all sensors
2023-01-28 J - Removed USB-C connector, wired JST-XH connector, PCB/Schematic first draft
2023-01-31 J - Updates based off of Phil feedback
2023-02-01 Add files via upload
    New version for sensor integration, moved everything out of main
2023-02-02 compartmentalized sensor stick
2023-02-02 current integration - missing barometer
2023-02-02 J - Current version with various changes according the feedback
2023-02-02 J - IMU changes
2023-02-07 Delete SensorStick_integrated.zip
    uploading new version
2023-02-11 Jesus - Edits to PCB schematic/layout
2023-02-17 Jesus- Up to date PCB sch/layout
2023-02-17 Jesus - Current version of IMU, functions implemented in USER Code 4 space
2023-02-22 Jesus - JLC DRC updates and .GBR/BOM/CPL files
2023-02-28 Jesus - Replaced prev IMU drivers
2023-02-28 Jesus - Removing old code
2023-02-28 Update main.c
    new method of reading
2023-03-07 interrupt based
2023-03-09 DMA version-untested
2023-03-09 Jesus - STM32CubeIDE proj for IMU DMA SPI
2023-03-17 Jesus - PCB version control
2023-04-06 Interrupt Version
    Messy but can clean up if need to transition, just wanted to get working
2023-04-12 new iteration based on hw/annas pcb
2023-04-12 Jesus - BMI)88 IMU Breakout Brd
2023-04-12 Jesus - Cleanup BMI088 folder
2023-04-12 Jesus - BMI088 Breakout Board Files
2023-04-12 Jesus - Edits to v1 for 2nd print
2023-04-12 Jesus - Init adaption of schematic for Proj. Drgnfy
2023-04-12 Jesus - More merge changes
2023-04-12 Jesus - Schematic should be complete
2023-04-12 Jesus - Updates to header pins on sch
2023-04-14 added oscillator
2023-04-14 J & N - Added TCXO to sch
2023-04-14 Jesus - BOM, CPL and gerber files added for v2
2023-04-19 Jesus - BMI088 IMU Drivers for STM32L476RG
2023-04-25 Jesus - Init files for final edits of PCB
2023-04-26 Jesus - Began to transition GPS to header pins
2023-04-26 Jesus - Cleaning up GPS schematic
2023-04-26 Add files via upload
    This is the integrated main.c, the sens_packet struct contains the packet format
2023-04-27 Jesus - Further updates to Mag/GPS/USART breakout
2023-04-27 Jesus - Cleaned up sch/layout, finished
2023-04-27 Jesus - Removed DIL24 IC connector
2023-04-27 Jesus - More sch cleanup, finalized
2023-04-27 Jesus - Rearranged to fit DIL24 socket for Mag breakout
2023-04-28 remove stubs
2023-04-28 fix uart header
2023-04-28 fuix gps header
2023-05-02 USB packet firmware added
2023-05-17 Jesus - Final edits to PCB, added holes and fixed spacing
2023-05-17 Jesus - Moved dfly to not cause probs
2023-05-22 MR-update talker_node
2023-05-25 Create README.md and sim folder
2023-05-25 working simulation with IMU gyro data
2023-05-25 updated firmware
2023-06-04 updated integrated code for prod
2023-06-05 MR-Update README.md
2023-06-09 files reworked

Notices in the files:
parts and their libraries:
SparkFun-Resistors: Licensing: Creative Commons ShareAlike 4.0 International - https://creativecommons.org/licenses/by-sa/4.0
COPYRIGHT: Copyright (C) 2023 Ultra Librarian. All rights reserved.
